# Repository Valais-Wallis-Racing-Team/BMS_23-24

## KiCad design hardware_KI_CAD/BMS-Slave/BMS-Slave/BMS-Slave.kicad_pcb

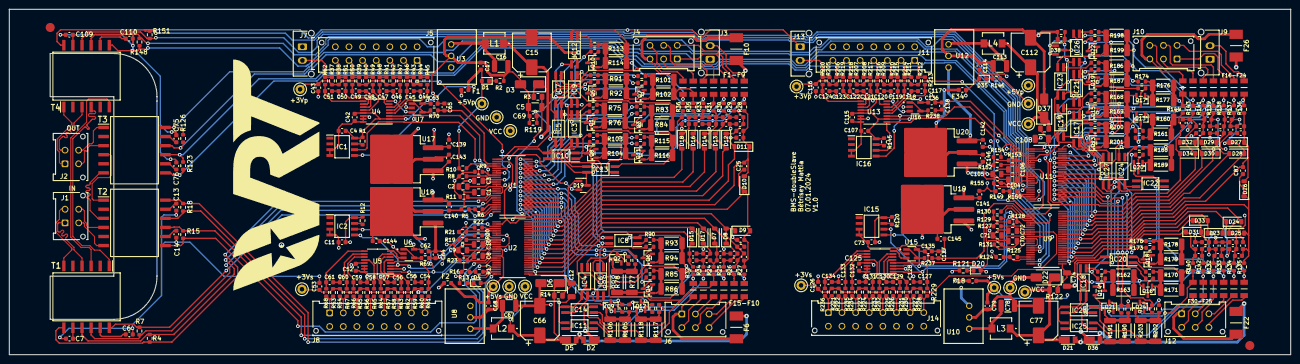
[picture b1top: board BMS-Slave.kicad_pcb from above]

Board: 4 copper layers, 282.0 x 76.0 mm, 568 parts (0 on the bottom side), 360 nets.

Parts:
C1, C2, C3, C8, C9, C10, C70, C71, C72, C104, C105, C106: 1uF/50V; C_0805_2012Metric
C4, C11, C17, C43, C53, C68, C73, C79, C107, C114, C116, C126, C139, C140, C141, C142: 100nF/50V; C_0603_1608Metric
C5, C12, C74, C108: 100nF/200V; C_1206_3216Metric
C6, C7, C13, C14, C75, C76, C109, C110: 100pF/50V; C_0603_1608Metric
C15, C66, C77, C112: 33uF/100V (8mm diameter); CP_Elec_8x10
C16, C67, C78, C113: 2.2uF/100V; C_1210_3225Metric
C18, C19, C20, C21, C22, C23, C24, C25, C26, C27, C28, C29, C30, C31, C32, C33, C34, C35, C36, C37, C38, C39, C40, C41, C44, C45, C46, C47, C48, C49, C50, C51, C54, C55, C56, C57, C58, C59, C60, C61, C64, C65, C80, C81, C82, C83, C84, C85, C86, C87, C88, C89, C90, C91, C92, C93, C94, C95, C96, C97, C98, C99, C100, C101, C102, C103, C117, C118, C119, C120, C121, C122, C123, C124, C127, C128, C129, C130, C131, C132, C133, C134, C137, C138: 10nF/100V; C_0603_1608Metric
C42, C52, C62, C63, C115, C125, C135, C136, C143, C144, C145, C146: 1uF/50V; C_0603_1608Metric
C69, C111: 10nF/50V; C_0603_1608Metric
D1, D4, D20, D35: LED Green TLMG1100-GS08; LED_0603_1608Metric
D2, D5, D21, D36: DFLS1100-7; POWERDI123_1
D3, D6, D22, D37: SMAJ54A-E3/61; D_SMA
D7, D8, D9, D10, D11, D12, D13, D14, D15, D16, D17, D18, D23, D24, D25, D26, D27, D28, D29, D30, D31, D32, D33, D34: SZMMSZ4692T1G; D_SOD-123
D19, D38: BAT54C,215; SOT-23
F1, F2, F18, F34: SF-0603SP063-2; Fuse_0603_1608Metric
F3, F4, F5, F7, F8, F9, F11, F12, F13, F14, F15, F16, F17, F19, F20, F21, F23, F24, F25, F27, F28, F29, F30, F31, F32, F33: 0466.250NR; FUSC3215X66N
F6, F10, F22, F26: 0448.500MR; FUSC6127X294N
FID1, FID2: Fiducial; fiducial 2mm with 3mm mask
IC1, IC2, IC15, IC16: M24M02-DWMN3TP_K; SOIC127P600X175-8N
IC3, IC4, IC5, IC6, IC7, IC8, IC9, IC10, IC11, IC12, IC13, IC14, IC17, IC18, IC19, IC20, IC21, IC22, IC23, IC24, IC25, IC26, IC27, IC28: ACPL-217-56BE; SOIC127P700X242-4N
J1, J2: 430450412; Molex_Micro-Fit_3.0_43045-0412_2x02_P3.00mm_Vertical
J3, J7, J9, J13: 43045-0212; Molex_Micro-Fit_3.0_43650-0215_1x02_P3.00mm_Vertical
J4, J6, J10, J12: Conn_01x06_Pin; Molex_Micro-Fit_3.0_43045-0612_2x03_P3.00mm_Vertical
J5, J11: Conn_01x14_Pin; Molex_Micro-Fit_3.0_43045-1412_2x07_P3.00mm_Vertical
J8, J14: Conn_01x16_Pin; Molex_Micro-Fit_3.0_43045-1612_2x08_P3.00mm_Vertical
L1, L2, L3, L4: 4.7uH; TCK176
Q1, Q2, Q3, Q4, Q5, Q6, Q7, Q8, Q9, Q10, Q11, Q12, Q13, Q14, Q15, Q16, Q17, Q18, Q19, Q20, Q21, Q22, Q23, Q24: NX2301P_215; SOT23_TO-236AB_NEX
R1, R10, R12, R21, R22, R37, R38, R39, R40, R41, R42, R43, R44, R53, R54, R55, R56, R57, R58, R59, R60, R119, R120, R129, R130, R145, R154, R204, R205, R206, R207, R208, R209, R210, R211, R212, R221, R222, R223, R224, R225, R226, R227, R228: 10k; R_0603_1608Metric
R2, R13, R121, R146: 270R; R_0603_1608Metric
R3, R14, R122, R147: 100R; R_0805_2012Metric
R4, R7, R15, R18, R123, R126, R148, R151: 120R; R_0603_1608Metric
R5, R8, R9, R16, R19, R20, R124, R127, R128, R149, R152, R153: 1k2; R_0603_1608Metric
R6, R17, R125, R150: 820R; R_0603_1608Metric
R11, R23, R131, R155: 1M; R_0603_1608Metric
R24, R25, R26, R27, R28, R29, R30, R31, R32, R33, R34, R35, R36, R45, R46, R47, R48, R49, R50, R51, R52, R61, R62, R63, R64, R65, R66, R67, R68, R69, R70, R132, R133, R134, R135, R136, R137, R138, R139, R140, R141, R142, R143, R144, R213, R214, R215, R216, R217, R218, R219, R220, R229, R230, R231, R232, R233, R234, R235, R236, R237, R238: 100R; R_0603_1608Metric
R71, R72, R79, R80, R87, R88, R95, R96, R97, R107, R108, R109, R156, R157, R164, R165, R172, R173, R180, R181, R182, R192, R193, R194: 3k3; R_0603_1608Metric
R73, R74, R81, R82, R89, R90, R98, R99, R100, R110, R111, R112, R158, R159, R166, R167, R174, R175, R183, R184, R185, R195, R196, R197: 150R; R_0603_1608Metric
R75, R76, R77, R78, R83, R84, R85, R86, R91, R92, R93, R94, R101, R102, R103, R104, R105, R106, R113, R114, R115, R116, R117, R118, R160, R161, R162, R163, R168, R169, R170, R171, R176, R177, R178, R179, R186, R187, R188, R189, R190, R191, R198, R199, R200, R201, R202, R203: 68R 1/3W; R_2010_5025Metric
T1, T2, T3, T4: HM2102NL; SOP200P1473X500-12N
TP1, TP2, TP3, TP4, TP5, TP6, TP7, TP8, TP9, TP10, TP11, TP12, TP13, TP14, TP15, TP16: TestPoint; TestPoint_Keystone_5000-5004_Miniature
U1, U2, U9, U11: LTC6811HG-1_PBF; SOP50P780X200-48N
U3, U8, U10, U12: TSR 0.6-4890WI; TSR 0.6-4850WI
U4, U5, U13, U14: ADG728BRUZ; TSSOP-16_4.4x5mm_P0.65mm
U6, U7, U15, U16: AD8628ARTZ-R2; SOT95P280X145-5N
U17, U18, U19, U20: LM1086ISX-5.0/NOPB; TO-263-3_TabPin2

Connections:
/slave1_of_2/EXT_DC_ISO_prim: C15.1, D2.1 (K), D3.1 (A1), L1.1, R3.1, TP4.1
/slave1_of_2/EXT_DC_ISO_sec: C66.1, D5.1 (K), D6.1 (A1), L2.1, R14.1, TP7.1
/slave1_of_2/GND: C1.2, C2.2, C3.2, C4.2, C5.2, C6.2, C7.2, C8.2, C9.2, C10.2, C11.2, C12.2, C13.2, C14.2, C15.2, C16.2, C17.1, C18.2, C20.2, C22.2, C24.2, C26.2, C28.2, C30.2, C32.2, C34.2, C36.2, C38.2, C40.2, C42.2, C43.2, C44.1, C45.1, C46.1, C47.1, C48.1, C49.1, C50.1, C51.1, C52.2, C53.2, C54.1, C55.1, C56.1, C57.1, C58.1, C59.1, C60.1, C61.1, C62.2, C63.2, C64.2, C65.2, C66.2, C67.2, C68.1, C69.2, C139.1, C140.1, C143.1, C144.1, D3.2 (A2), D6.2 (A2), F10.2, IC1.3 (E2), IC1.4 (VSS), IC2.3 (E2), IC2.4 (VSS), J5.8, J5.9, J5.10, J5.11, J5.12, J5.13, J5.14, J7.1, J8.9, J8.10, J8.11, J8.12, J8.13, J8.14, J8.15, J8.16, R2.2, R5.2, R13.2, R16.2, R119.2, TP5.1, TP8.1, U1.30 (V-), U1.31 (V-__1), U2.30 (V-), U2.31 (V-__1), U2.36 (DTEN), U3.2 (GND), U4.14 (GND), U4.15 (A1), U4.16 (A0), U5.14 (GND), U5.15 (A1), U5.16 (A0), U6.2, U7.2, U8.2 (GND), U17.1 (GND), U18.1 (GND)
/slave1_of_2/SCL1: IC1.6 (SCL), R8.2, U1.33 (GPIO5), U4.1 (SCL)
/slave1_of_2/SCL2: IC2.6 (SCL), R19.2, U2.33 (GPIO5), U5.1 (SCL)
/slave1_of_2/SDA1: IC1.5 (SDA), R9.2, U1.32 (GPIO4), U4.3 (SDA)
/slave1_of_2/SDA2: IC2.5 (SDA), R20.2, U2.32 (GPIO4), U5.3 (SDA)
/slave1_of_2/Temp_MUX_prim: C65.1, R70.2, U1.27 (GPIO1)
/slave1_of_2/Temp_MUX_sec: C64.1, R69.2, U2.27 (GPIO1)
/slave1_of_2/U_Analog_IN/OPA_TEMP_prim: U4.8 (D), U7.3
/slave1_of_2/U_Analog_IN/OPA_TEMP_sec: U5.8 (D), U6.3
/slave1_of_2/U_Analog_IN/T_sens0: J5.1, R44.2, R45.1
/slave1_of_2/U_Analog_IN/T_sens1: J5.2, R43.2, R46.1
/slave1_of_2/U_Analog_IN/T_sens2: J5.3, R42.2, R47.1
/slave1_of_2/U_Analog_IN/T_sens3: J5.4, R41.2, R48.1
/slave1_of_2/U_Analog_IN/T_sens4: J5.5, R40.2, R49.1
/slave1_of_2/U_Analog_IN/T_sens5: J5.6, R39.2, R50.1
/slave1_of_2/U_Analog_IN/T_sens6: J5.7, R38.2, R51.1
/slave1_of_2/U_Analog_IN/T_sens7: J7.2, R37.2, R52.1
/slave1_of_2/U_Analog_IN/T_sens8: J8.8, R60.2, R61.1
/slave1_of_2/U_Analog_IN/T_sens9: J8.7, R59.2, R62.1
/slave1_of_2/U_Analog_IN/T_sens10: J8.6, R58.2, R63.1
/slave1_of_2/U_Analog_IN/T_sens11: J8.5, R57.2, R64.1
/slave1_of_2/U_Analog_IN/T_sens12: J8.4, R56.2, R65.1
/slave1_of_2/U_Analog_IN/T_sens13: J8.3, R55.2, R66.1
/slave1_of_2/U_Analog_IN/T_sens14: J8.2, R54.2, R67.1
/slave1_of_2/U_Analog_IN/T_sens15: J8.1, R53.2, R68.1
/slave1_of_2/U_Connectors/Cell.0: F4.1, J4.6
/slave1_of_2/U_Connectors/Cell.1: F5.1, J4.2
/slave1_of_2/U_Connectors/Cell.2: F7.1, J4.5
/slave1_of_2/U_Connectors/Cell.3: F8.1, J4.1
/slave1_of_2/U_Connectors/Cell.4: F9.1, J4.4
/slave1_of_2/U_Connectors/Cell.5: F11.1, J3.2
/slave1_of_2/U_Connectors/Cell.6: F12.1, J6.6
/slave1_of_2/U_Connectors/Cell.7: F13.1, J6.3
/slave1_of_2/U_Connectors/Cell.8: F14.1, J6.5
/slave1_of_2/U_Connectors/Cell.9: F15.1, J6.2
/slave1_of_2/U_Connectors/Cell.10: F16.1, J6.4
/slave1_of_2/U_Connectors/Cell.11: F6.1, F17.1, J6.1
/slave1_of_2/U_Connectors/Cell.GND: F3.1, F10.1, J4.3
/slave1_of_2/U_Input_Fuses/Cell_Fused.0: F4.2, IC9.2 (K), Q10.2 (S), R35.1, R101.2, R102.2
/slave1_of_2/U_Input_Fuses/Cell_Fused.1: F5.2, IC7.2 (K), Q7.2 (S), R33.1, R91.2, R92.2
/slave1_of_2/U_Input_Fuses/Cell_Fused.2: F7.2, IC5.2 (K), Q5.2 (S), R31.1, R83.2, R84.2
/slave1_of_2/U_Input_Fuses/Cell_Fused.3: F8.2, IC3.2 (K), Q3.2 (S), R30.1, R75.2, R76.2
/slave1_of_2/U_Input_Fuses/Cell_Fused.4: F9.2, IC13.2 (K), Q1.2 (S), R29.1, R115.2, R116.2
/slave1_of_2/U_Input_Fuses/Cell_Fused.5: F11.2, IC10.2 (K), Q11.2 (S), R28.1, R103.2, R104.2
/slave1_of_2/U_Input_Fuses/Cell_Fused.6: F12.2, IC8.2 (K), Q8.2 (S), R27.1, R93.2, R94.2
/slave1_of_2/U_Input_Fuses/Cell_Fused.7: F13.2, IC6.2 (K), Q6.2 (S), R26.1, R85.2, R86.2
/slave1_of_2/U_Input_Fuses/Cell_Fused.8: F14.2, IC4.2 (K), Q4.2 (S), R25.1, R77.2, R78.2
/slave1_of_2/U_Input_Fuses/Cell_Fused.9: F15.2, IC14.2 (K), Q2.2 (S), R24.1, R117.2, R118.2
/slave1_of_2/U_Input_Fuses/Cell_Fused.10: F16.2, IC11.2 (K), Q12.2 (S), R34.1, R105.2, R106.2
/slave1_of_2/U_Input_Fuses/Cell_Fused.11: F17.2, Q9.2 (S), R32.1
/slave1_of_2/U_Input_Fuses/Cell_Fused.GND: F3.2, IC12.2 (K), R36.1, R113.2, R114.2
/slave1_of_2/U_Passive_Balancing/GLOBAL_BAL_FEEDBACK: C69.1, IC3.3 (E), IC4.3 (E), IC5.3 (E), IC6.3 (E), IC7.3 (E), IC8.3 (E), IC9.3 (E), IC10.3 (E), IC11.3 (E), IC12.3 (E), IC13.3 (E), IC14.3 (E), R119.1, U1.29 (GPIO3)
/slave1_of_2/U_Passive_Balancing/S1: R107.2, U1.25 (S1)
/slave1_of_2/U_Passive_Balancing/S2: R95.2, U1.23 (S2)
/slave1_of_2/U_Passive_Balancing/S3: R87.2, U1.21 (S3)
/slave1_of_2/U_Passive_Balancing/S4: R79.2, U1.19 (S4)
/slave1_of_2/U_Passive_Balancing/S5: R71.2, U1.17 (S5)
/slave1_of_2/U_Passive_Balancing/S6: R108.2, U1.15 (S6)
/slave1_of_2/U_Passive_Balancing/S7: R96.2, U1.13 (S7)
/slave1_of_2/U_Passive_Balancing/S8: R88.2, U1.11 (S8)
/slave1_of_2/U_Passive_Balancing/S9: R80.2, U1.9 (S9)
/slave1_of_2/U_Passive_Balancing/S10: R72.2, U1.7 (S10)
/slave1_of_2/U_Passive_Balancing/S11: R109.2, U1.5 (S11)
/slave1_of_2/U_Passive_Balancing/S12: R97.2, U1.3 (S12)
/slave1_of_2/U_Primary_ADBMS/C0: C41.2, D18.2 (A), R36.2, U1.26 (C0), U2.26 (C0)
/slave1_of_2/U_Primary_ADBMS/C1: C37.2, C40.1, C41.1, D16.2 (A), D18.1 (K), R35.2, U1.24 (C1), U2.24 (C1)
/slave1_of_2/U_Primary_ADBMS/C2: C33.2, C36.1, C37.1, D14.2 (A), D16.1 (K), R33.2, U1.22 (C2), U2.22 (C2)
/slave1_of_2/U_Primary_ADBMS/C3: C31.2, C32.1, C33.1, D13.2 (A), D14.1 (K), R31.2, U1.20 (C3), U2.20 (C3)
/slave1_of_2/U_Primary_ADBMS/C4: C29.2, C30.1, C31.1, D12.2 (A), D13.1 (K), R30.2, U1.18 (C4), U2.18 (C4)
/slave1_of_2/U_Primary_ADBMS/C5: C27.2, C28.1, C29.1, D11.2 (A), D12.1 (K), R29.2, U1.16 (C5), U2.16 (C5)
/slave1_of_2/U_Primary_ADBMS/C6: C25.2, C26.1, C27.1, D10.2 (A), D11.1 (K), R28.2, U1.14 (C6), U2.14 (C6)
/slave1_of_2/U_Primary_ADBMS/C7: C23.2, C24.1, C25.1, D9.2 (A), D10.1 (K), R27.2, U1.12 (C7), U2.12 (C7)
/slave1_of_2/U_Primary_ADBMS/C8: C21.2, C22.1, C23.1, D8.2 (A), D9.1 (K), R26.2, U1.10 (C8), U2.10 (C8)
/slave1_of_2/U_Primary_ADBMS/C9: C19.2, C20.1, C21.1, D7.2 (A), D8.1 (K), R25.2, U1.8 (C9), U2.8 (C9)
/slave1_of_2/U_Primary_ADBMS/C10: C18.1, C19.1, C39.2, D7.1 (K), D17.2 (A), R24.2, U1.6 (C10), U2.6 (C10)
/slave1_of_2/U_Primary_ADBMS/C11: C35.2, C38.1, C39.1, D15.2 (A), D17.1 (K), R34.2, U1.4 (C11), U2.4 (C11)
/slave1_of_2/U_Primary_ADBMS/C12: C34.1, C35.1, D15.1 (K), R32.2, U1.2 (C12), U2.2 (C12)
/slave1_of_2/U_Primary_ADBMS/IN_M1: R4.1, T1.7 (SEC_1), U1.41 (CSB/IMA)
/slave1_of_2/U_Primary_ADBMS/IN_P1: R4.2, T1.9 (SEC_3), U1.42 (SCK/IPA)
/slave1_of_2/U_Primary_ADBMS/OUT_M1: R7.1, T1.10 (SEC_4), U1.47 (IMB)
/slave1_of_2/U_Primary_ADBMS/OUT_P1: R7.2, T1.12 (SEC_6), U1.48 (IPB)
/slave1_of_2/U_Primary_ADBMS/isoSPI_IN+: J1.1, T1.4 (PRI_4)
/slave1_of_2/U_Primary_ADBMS/isoSPI_IN-: J1.2, T1.6 (PRI_6)
/slave1_of_2/U_Primary_ADBMS/isoSPI_OUT+: T1.1 (PRI_1), T4.4 (PRI_4)
/slave1_of_2/U_Primary_ADBMS/isoSPI_OUT-: T1.3 (PRI_3), T4.6 (PRI_6)
/slave1_of_2/U_Primary_ADBMS/prim3V3: C2.1, U1.35 (VREF1)
/slave1_of_2/U_Secondary_ADBMS/IN_M1: R15.1, T2.7 (SEC_1), U2.41 (CSB/IMA)
/slave1_of_2/U_Secondary_ADBMS/IN_P1: R15.2, T2.9 (SEC_3), U2.42 (SCK/IPA)
/slave1_of_2/U_Secondary_ADBMS/OUT_M1: R18.1, T2.10 (SEC_4), U2.47 (IMB)
/slave1_of_2/U_Secondary_ADBMS/OUT_P1: R18.2, T2.12 (SEC_6), U2.48 (IPB)
/slave1_of_2/U_Secondary_ADBMS/isoSPI_IN+: J1.4, T2.4 (PRI_4)
/slave1_of_2/U_Secondary_ADBMS/isoSPI_IN-: J1.3, T2.6 (PRI_6)
/slave1_of_2/U_Secondary_ADBMS/isoSPI_OUT+: T2.1 (PRI_1), T3.4 (PRI_4)
/slave1_of_2/U_Secondary_ADBMS/isoSPI_OUT-: T2.3 (PRI_3), T3.6 (PRI_6)
/slave1_of_2/U_Secondary_ADBMS/sec3v3: C9.1, U2.35 (VREF1)
/slave1_of_2/VBAT+: D2.2 (A), D5.2 (A), F6.2
/slave1_of_2/prim+3V: C3.1, C43.1, R37.1, R38.1, R39.1, R40.1, R41.1, R42.1, R43.1, R44.1, TP1.1, U1.34 (VREF2)
/slave1_of_2/prim+5V: C1.1, C4.1, C17.2, C42.1, C63.1, D1.2 (A), D19.2, F1.1, IC1.8 (VCC), R1.1, R8.1, R9.1, R10.1, R11.1, TP3.1, U1.36 (DTEN), U1.37 (VREG), U1.40 (ISOMD), U4.2 (~RESET), U4.13 (VDD), U7.5
/slave1_of_2/sec+3v: C10.1, C53.1, R53.1, R54.1, R55.1, R56.1, R57.1, R58.1, R59.1, R60.1, TP2.1, U2.34 (VREF2)
/slave1_of_2/sec+5v: C8.1, C11.1, C52.1, C62.1, C68.2, D4.2 (A), D19.1, F2.1, IC2.8 (VCC), R12.1, R19.1, R20.1, R21.1, R22.1, R23.1, TP6.1, U2.37 (VREG), U2.40 (ISOMD), U5.2 (~RESET), U5.13 (VDD), U6.5
/slave2_of_2/EXT_DC_ISO_prim: C112.1, D36.1 (K), D37.1 (A1), L4.1, R147.1, TP15.1
/slave2_of_2/EXT_DC_ISO_sec: C77.1, D21.1 (K), D22.1 (A1), L3.1, R122.1, TP11.1
/slave2_of_2/GND: C70.2, C71.2, C72.2, C73.2, C74.2, C75.2, C76.2, C77.2, C78.2, C79.1, C80.2, C82.2, C84.2, C86.2, C88.2, C90.2, C92.2, C94.2, C96.2, C98.2, C100.2, C102.2, C104.2, C105.2, C106.2, C107.2, C108.2, C109.2, C110.2, C111.2, C112.2, C113.2, C114.1, C115.2, C116.2, C117.1, C118.1, C119.1, C120.1, C121.1, C122.1, C123.1, C124.1, C125.2, C126.2, C127.1, C128.1, C129.1, C130.1, C131.1, C132.1, C133.1, C134.1, C135.2, C136.2, C137.2, C138.2, C141.1, C142.1, C145.1, C146.1, D22.2 (A2), D37.2 (A2), F26.2, IC15.3 (E2), IC15.4 (VSS), IC16.3 (E2), IC16.4 (VSS), J11.8, J11.9, J11.10, J11.11, J11.12, J11.13, J11.14, J13.1, J14.9, J14.10, J14.11, J14.12, J14.13, J14.14, J14.15, J14.16, R121.2, R124.2, R146.2, R149.2, R204.2, TP12.1, TP16.1, U9.30 (V-), U9.31 (V-__1), U9.36 (DTEN), U10.2 (GND), U11.30 (V-), U11.31 (V-__1), U12.2 (GND), U13.14 (GND), U13.15 (A1), U13.16 (A0), U14.14 (GND), U14.15 (A1), U14.16 (A0), U15.2, U16.2, U19.1 (GND), U20.1 (GND)
/slave2_of_2/SCL1: IC16.6 (SCL), R152.2, U11.33 (GPIO5), U13.1 (SCL)
/slave2_of_2/SCL2: IC15.6 (SCL), R127.2, U9.33 (GPIO5), U14.1 (SCL)
/slave2_of_2/SDA1: IC16.5 (SDA), R153.2, U11.32 (GPIO4), U13.3 (SDA)
/slave2_of_2/SDA2: IC15.5 (SDA), R128.2, U9.32 (GPIO4), U14.3 (SDA)
/slave2_of_2/Temp_MUX_prim: C138.1, R238.2, U11.27 (GPIO1)
/slave2_of_2/Temp_MUX_sec: C137.1, R237.2, U9.27 (GPIO1)
/slave2_of_2/U_Analog_IN/OPA_TEMP_prim: U13.8 (D), U16.3
/slave2_of_2/U_Analog_IN/OPA_TEMP_sec: U14.8 (D), U15.3
/slave2_of_2/U_Analog_IN/T_sens0: J11.1, R212.2, R213.1
/slave2_of_2/U_Analog_IN/T_sens1: J11.2, R211.2, R214.1
/slave2_of_2/U_Analog_IN/T_sens2: J11.3, R210.2, R215.1
/slave2_of_2/U_Analog_IN/T_sens3: J11.4, R209.2, R216.1
/slave2_of_2/U_Analog_IN/T_sens4: J11.5, R208.2, R217.1
/slave2_of_2/U_Analog_IN/T_sens5: J11.6, R207.2, R218.1
/slave2_of_2/U_Analog_IN/T_sens6: J11.7, R206.2, R219.1
/slave2_of_2/U_Analog_IN/T_sens7: J13.2, R205.2, R220.1
/slave2_of_2/U_Analog_IN/T_sens8: J14.8, R228.2, R229.1
/slave2_of_2/U_Analog_IN/T_sens9: J14.7, R227.2, R230.1
/slave2_of_2/U_Analog_IN/T_sens10: J14.6, R226.2, R231.1
/slave2_of_2/U_Analog_IN/T_sens11: J14.5, R225.2, R232.1
/slave2_of_2/U_Analog_IN/T_sens12: J14.4, R224.2, R233.1
/slave2_of_2/U_Analog_IN/T_sens13: J14.3, R223.2, R234.1
/slave2_of_2/U_Analog_IN/T_sens14: J14.2, R222.2, R235.1
/slave2_of_2/U_Analog_IN/T_sens15: J14.1, R221.2, R236.1
/slave2_of_2/U_Connectors/Cell.0: F20.1, J10.6
/slave2_of_2/U_Connectors/Cell.1: F21.1, J10.2
/slave2_of_2/U_Connectors/Cell.2: F23.1, J10.5
/slave2_of_2/U_Connectors/Cell.3: F24.1, J10.1
/slave2_of_2/U_Connectors/Cell.4: F25.1, J10.4
/slave2_of_2/U_Connectors/Cell.5: F27.1, J9.2
/slave2_of_2/U_Connectors/Cell.6: F28.1, J12.6
/slave2_of_2/U_Connectors/Cell.7: F29.1, J12.3
/slave2_of_2/U_Connectors/Cell.8: F30.1, J12.5
/slave2_of_2/U_Connectors/Cell.9: F31.1, J12.2
/slave2_of_2/U_Connectors/Cell.10: F32.1, J12.4
/slave2_of_2/U_Connectors/Cell.11: F22.1, F33.1, J12.1
/slave2_of_2/U_Connectors/Cell.GND: F19.1, F26.1, J10.3
/slave2_of_2/U_Input_Fuses/Cell_Fused.0: F20.2, IC23.2 (K), Q22.2 (S), R143.1, R186.2, R187.2
/slave2_of_2/U_Input_Fuses/Cell_Fused.1: F21.2, IC21.2 (K), Q19.2 (S), R141.1, R176.2, R177.2
/slave2_of_2/U_Input_Fuses/Cell_Fused.2: F23.2, IC19.2 (K), Q17.2 (S), R139.1, R168.2, R169.2
/slave2_of_2/U_Input_Fuses/Cell_Fused.3: F24.2, IC17.2 (K), Q15.2 (S), R138.1, R160.2, R161.2
/slave2_of_2/U_Input_Fuses/Cell_Fused.4: F25.2, IC27.2 (K), Q13.2 (S), R137.1, R200.2, R201.2
/slave2_of_2/U_Input_Fuses/Cell_Fused.5: F27.2, IC24.2 (K), Q23.2 (S), R136.1, R188.2, R189.2
/slave2_of_2/U_Input_Fuses/Cell_Fused.6: F28.2, IC22.2 (K), Q20.2 (S), R135.1, R178.2, R179.2
/slave2_of_2/U_Input_Fuses/Cell_Fused.7: F29.2, IC20.2 (K), Q18.2 (S), R134.1, R170.2, R171.2
/slave2_of_2/U_Input_Fuses/Cell_Fused.8: F30.2, IC18.2 (K), Q16.2 (S), R133.1, R162.2, R163.2
/slave2_of_2/U_Input_Fuses/Cell_Fused.9: F31.2, IC28.2 (K), Q14.2 (S), R132.1, R202.2, R203.2
/slave2_of_2/U_Input_Fuses/Cell_Fused.10: F32.2, IC25.2 (K), Q24.2 (S), R142.1, R190.2, R191.2
/slave2_of_2/U_Input_Fuses/Cell_Fused.11: F33.2, Q21.2 (S), R140.1
/slave2_of_2/U_Input_Fuses/Cell_Fused.GND: F19.2, IC26.2 (K), R144.1, R198.2, R199.2
/slave2_of_2/U_Passive_Balancing/GLOBAL_BAL_FEEDBACK: C111.1, IC17.3 (E), IC18.3 (E), IC19.3 (E), IC20.3 (E), IC21.3 (E), IC22.3 (E), IC23.3 (E), IC24.3 (E), IC25.3 (E), IC26.3 (E), IC27.3 (E), IC28.3 (E), R204.1, U11.29 (GPIO3)
/slave2_of_2/U_Passive_Balancing/S1: R192.2, U11.25 (S1)
/slave2_of_2/U_Passive_Balancing/S2: R180.2, U11.23 (S2)
/slave2_of_2/U_Passive_Balancing/S3: R172.2, U11.21 (S3)
/slave2_of_2/U_Passive_Balancing/S4: R164.2, U11.19 (S4)
/slave2_of_2/U_Passive_Balancing/S5: R156.2, U11.17 (S5)
/slave2_of_2/U_Passive_Balancing/S6: R193.2, U11.15 (S6)
/slave2_of_2/U_Passive_Balancing/S7: R181.2, U11.13 (S7)
/slave2_of_2/U_Passive_Balancing/S8: R173.2, U11.11 (S8)
/slave2_of_2/U_Passive_Balancing/S9: R165.2, U11.9 (S9)
/slave2_of_2/U_Passive_Balancing/S10: R157.2, U11.7 (S10)
/slave2_of_2/U_Passive_Balancing/S11: R194.2, U11.5 (S11)
/slave2_of_2/U_Passive_Balancing/S12: R182.2, U11.3 (S12)
/slave2_of_2/U_Primary_ADBMS/C0: C103.2, D34.2 (A), R144.2, U9.26 (C0), U11.26 (C0)
/slave2_of_2/U_Primary_ADBMS/C1: C99.2, C102.1, C103.1, D32.2 (A), D34.1 (K), R143.2, U9.24 (C1), U11.24 (C1)
/slave2_of_2/U_Primary_ADBMS/C2: C95.2, C98.1, C99.1, D30.2 (A), D32.1 (K), R141.2, U9.22 (C2), U11.22 (C2)
/slave2_of_2/U_Primary_ADBMS/C3: C93.2, C94.1, C95.1, D29.2 (A), D30.1 (K), R139.2, U9.20 (C3), U11.20 (C3)
/slave2_of_2/U_Primary_ADBMS/C4: C91.2, C92.1, C93.1, D28.2 (A), D29.1 (K), R138.2, U9.18 (C4), U11.18 (C4)
/slave2_of_2/U_Primary_ADBMS/C5: C89.2, C90.1, C91.1, D27.2 (A), D28.1 (K), R137.2, U9.16 (C5), U11.16 (C5)
/slave2_of_2/U_Primary_ADBMS/C6: C87.2, C88.1, C89.1, D26.2 (A), D27.1 (K), R136.2, U9.14 (C6), U11.14 (C6)
/slave2_of_2/U_Primary_ADBMS/C7: C85.2, C86.1, C87.1, D25.2 (A), D26.1 (K), R135.2, U9.12 (C7), U11.12 (C7)
/slave2_of_2/U_Primary_ADBMS/C8: C83.2, C84.1, C85.1, D24.2 (A), D25.1 (K), R134.2, U9.10 (C8), U11.10 (C8)
/slave2_of_2/U_Primary_ADBMS/C9: C81.2, C82.1, C83.1, D23.2 (A), D24.1 (K), R133.2, U9.8 (C9), U11.8 (C9)
/slave2_of_2/U_Primary_ADBMS/C10: C80.1, C81.1, C101.2, D23.1 (K), D33.2 (A), R132.2, U9.6 (C10), U11.6 (C10)
/slave2_of_2/U_Primary_ADBMS/C11: C97.2, C100.1, C101.1, D31.2 (A), D33.1 (K), R142.2, U9.4 (C11), U11.4 (C11)
/slave2_of_2/U_Primary_ADBMS/C12: C96.1, C97.1, D31.1 (K), R140.2, U9.2 (C12), U11.2 (C12)
/slave2_of_2/U_Primary_ADBMS/IN_M1: R148.1, T4.7 (SEC_1), U11.41 (CSB/IMA)
/slave2_of_2/U_Primary_ADBMS/IN_P1: R148.2, T4.9 (SEC_3), U11.42 (SCK/IPA)
/slave2_of_2/U_Primary_ADBMS/OUT_M1: R151.1, T4.10 (SEC_4), U11.47 (IMB)
/slave2_of_2/U_Primary_ADBMS/OUT_P1: R151.2, T4.12 (SEC_6), U11.48 (IPB)
/slave2_of_2/U_Primary_ADBMS/isoSPI_OUT+: J2.1, T4.1 (PRI_1)
/slave2_of_2/U_Primary_ADBMS/isoSPI_OUT-: J2.2, T4.3 (PRI_3)
/slave2_of_2/U_Primary_ADBMS/prim3V3: C105.1, U11.35 (VREF1)
/slave2_of_2/U_Secondary_ADBMS/IN_M1: R123.1, T3.7 (SEC_1), U9.41 (CSB/IMA)
/slave2_of_2/U_Secondary_ADBMS/IN_P1: R123.2, T3.9 (SEC_3), U9.42 (SCK/IPA)
/slave2_of_2/U_Secondary_ADBMS/OUT_M1: R126.1, T3.10 (SEC_4), U9.47 (IMB)
/slave2_of_2/U_Secondary_ADBMS/OUT_P1: R126.2, T3.12 (SEC_6), U9.48 (IPB)
/slave2_of_2/U_Secondary_ADBMS/isoSPI_OUT+: J2.4, T3.1 (PRI_1)
/slave2_of_2/U_Secondary_ADBMS/isoSPI_OUT-: J2.3, T3.3 (PRI_3)
/slave2_of_2/U_Secondary_ADBMS/sec3v3: C71.1, U9.35 (VREF1)
/slave2_of_2/VBAT+: D21.2 (A), D36.2 (A), F22.2
/slave2_of_2/prim+3V: C106.1, C116.1, R205.1, R206.1, R207.1, R208.1, R209.1, R210.1, R211.1, R212.1, TP13.1, U11.34 (VREF2)
/slave2_of_2/prim+5V: C104.1, C107.1, C114.2, C115.1, C136.1, D35.2 (A), D38.2, F34.1, IC16.8 (VCC), R145.1, R152.1, R153.1, R154.1, R155.1, TP14.1, U11.36 (DTEN), U11.37 (VREG), U11.40 (ISOMD), U13.2 (~RESET), U13.13 (VDD), U16.5
/slave2_of_2/sec+3v: C72.1, C126.1, R221.1, R222.1, R223.1, R224.1, R225.1, R226.1, R227.1, R228.1, TP9.1, U9.34 (VREF2)
/slave2_of_2/sec+5v: C70.1, C73.1, C79.2, C125.1, C135.1, D20.2 (A), D38.1, F18.1, IC15.8 (VCC), R120.1, R127.1, R128.1, R129.1, R130.1, R131.1, TP10.1, U9.37 (VREG), U9.40 (ISOMD), U14.2 (~RESET), U14.13 (VDD), U15.5
unnamed: D1.1 (K), R2.1
unnamed: D4.1 (K), R13.1
unnamed: D20.1 (K), R121.1
unnamed: D35.1 (K), R146.1
unnamed: IC1.7 (~WC), R1.2
unnamed: IC2.7 (~WC), R12.2
unnamed: IC3.1 (A), R73.2
unnamed: IC4.1 (A), R74.2
unnamed: IC5.1 (A), R81.2
unnamed: IC6.1 (A), R82.2
unnamed: IC7.1 (A), R89.2
unnamed: IC8.1 (A), R90.2
unnamed: IC9.1 (A), R98.2
unnamed: IC10.1 (A), R99.2
unnamed: D19.3, IC3.4 (C), IC4.4 (C), IC5.4 (C), IC6.4 (C), IC7.4 (C), IC8.4 (C), IC9.4 (C), IC10.4 (C), IC11.4 (C), IC12.4 (C), IC13.4 (C), IC14.4 (C)
unnamed: IC11.1 (A), R100.2
unnamed: IC12.1 (A), R110.2
unnamed: IC13.1 (A), R111.2
unnamed: IC14.1 (A), R112.2
unnamed: IC15.7 (~WC), R120.2
unnamed: IC16.7 (~WC), R145.2
unnamed: IC17.1 (A), R158.2
unnamed: D38.3, IC17.4 (C), IC18.4 (C), IC19.4 (C), IC20.4 (C), IC21.4 (C), IC22.4 (C), IC23.4 (C), IC24.4 (C), IC25.4 (C), IC26.4 (C), IC27.4 (C), IC28.4 (C)
unnamed: IC18.1 (A), R159.2
unnamed: IC19.1 (A), R166.2
unnamed: IC20.1 (A), R167.2
unnamed: IC21.1 (A), R174.2
unnamed: IC22.1 (A), R175.2
unnamed: IC23.1 (A), R183.2
unnamed: IC24.1 (A), R184.2
unnamed: IC25.1 (A), R185.2
unnamed: IC26.1 (A), R195.2
unnamed: IC27.1 (A), R196.2
unnamed: IC28.1 (A), R197.2
unnamed: Q1.1 (D), R73.1, R75.1, R76.1
unnamed: Q1.3 (G), R71.1
unnamed: Q2.1 (D), R74.1, R77.1, R78.1
unnamed: Q2.3 (G), R72.1
unnamed: Q3.1 (D), R81.1, R83.1, R84.1
unnamed: Q3.3 (G), R79.1
unnamed: Q4.1 (D), R82.1, R85.1, R86.1
unnamed: Q4.3 (G), R80.1
unnamed: Q5.1 (D), R89.1, R91.1, R92.1
unnamed: Q5.3 (G), R87.1
unnamed: Q6.1 (D), R90.1, R93.1, R94.1
unnamed: Q6.3 (G), R88.1
unnamed: Q7.1 (D), R98.1, R101.1, R102.1
unnamed: Q7.3 (G), R95.1
unnamed: Q8.1 (D), R99.1, R103.1, R104.1
unnamed: Q8.3 (G), R96.1
unnamed: Q9.1 (D), R100.1, R105.1, R106.1
unnamed: Q9.3 (G), R97.1
unnamed: Q10.1 (D), R110.1, R113.1, R114.1
unnamed: Q10.3 (G), R107.1
unnamed: Q11.1 (D), R111.1, R115.1, R116.1
unnamed: Q11.3 (G), R108.1
unnamed: Q12.1 (D), R112.1, R117.1, R118.1
unnamed: Q12.3 (G), R109.1
unnamed: Q13.1 (D), R158.1, R160.1, R161.1
unnamed: Q13.3 (G), R156.1
unnamed: Q14.1 (D), R159.1, R162.1, R163.1
unnamed: Q14.3 (G), R157.1
unnamed: Q15.1 (D), R166.1, R168.1, R169.1
unnamed: Q15.3 (G), R164.1
unnamed: Q16.1 (D), R167.1, R170.1, R171.1
unnamed: Q16.3 (G), R165.1
unnamed: Q17.1 (D), R174.1, R176.1, R177.1
unnamed: Q17.3 (G), R172.1
unnamed: Q18.1 (D), R175.1, R178.1, R179.1
unnamed: Q18.3 (G), R173.1
unnamed: Q19.1 (D), R183.1, R186.1, R187.1
unnamed: Q19.3 (G), R180.1
unnamed: Q20.1 (D), R184.1, R188.1, R189.1
unnamed: Q20.3 (G), R181.1
unnamed: Q21.1 (D), R185.1, R190.1, R191.1
unnamed: Q21.3 (G), R182.1
unnamed: Q22.1 (D), R195.1, R198.1, R199.1
unnamed: Q22.3 (G), R192.1
unnamed: Q23.1 (D), R196.1, R200.1, R201.1
unnamed: Q23.3 (G), R193.1
unnamed: Q24.1 (D), R197.1, R202.1, R203.1
unnamed: Q24.3 (G), R194.1
unnamed: R69.1, U6.1, U6.4
unnamed: R70.1, U7.1, U7.4
unnamed: R237.1, U15.1, U15.4
unnamed: R238.1, U16.1, U16.4
unnamed: C7.1, T1.8 (SEC_2)
unnamed: C6.1, T1.11 (SEC_5)
unnamed: C14.1, T2.8 (SEC_2)
unnamed: C13.1, T2.11 (SEC_5)
unnamed: C76.1, T3.8 (SEC_2)
unnamed: C75.1, T3.11 (SEC_5)
unnamed: C110.1, T4.8 (SEC_2)
unnamed: C109.1, T4.11 (SEC_5)
unnamed: R10.2, U1.28 (GPIO2)
unnamed: R6.2, U1.45 (IBIAS)
unnamed: R5.1, R6.1, U1.46 (ICMP)
unnamed: C5.1, R3.2, U1.1 (V+)
unnamed: R11.2, U1.39 (WDT)
unnamed: R22.2, U2.28 (GPIO2)
unnamed: R21.2, U2.29 (GPIO3)
unnamed: R17.2, U2.45 (IBIAS)
unnamed: R16.1, R17.1, U2.46 (ICMP)
unnamed: C12.1, R14.2, U2.1 (V+)
unnamed: R23.2, U2.39 (WDT)
unnamed: C16.1, L1.2, U3.1 (+VIN)
unnamed: C44.2, R45.2, U4.4 (S1)
unnamed: C45.2, R46.2, U4.5 (S2)
unnamed: C46.2, R47.2, U4.6 (S3)
unnamed: C47.2, R48.2, U4.7 (S4)
unnamed: C48.2, R49.2, U4.12 (S5)
unnamed: C49.2, R50.2, U4.11 (S6)
unnamed: C50.2, R51.2, U4.10 (S7)
unnamed: C51.2, R52.2, U4.9 (S8)
unnamed: C54.2, R61.2, U5.4 (S1)
unnamed: C55.2, R62.2, U5.5 (S2)
unnamed: C56.2, R63.2, U5.6 (S3)
unnamed: C57.2, R64.2, U5.7 (S4)
unnamed: C58.2, R65.2, U5.12 (S5)
unnamed: C59.2, R66.2, U5.11 (S6)
unnamed: C60.2, R67.2, U5.10 (S7)
unnamed: C61.2, R68.2, U5.9 (S8)
unnamed: C67.1, L2.2, U8.1 (+VIN)
unnamed: R130.2, U9.28 (GPIO2)
unnamed: R129.2, U9.29 (GPIO3)
unnamed: R125.2, U9.45 (IBIAS)
unnamed: R124.1, R125.1, U9.46 (ICMP)
unnamed: C74.1, R122.2, U9.1 (V+)
unnamed: R131.2, U9.39 (WDT)
unnamed: C78.1, L3.2, U10.1 (+VIN)
unnamed: C141.2, U10.3 (+VOUT), U19.3 (VI)
unnamed: R154.2, U11.28 (GPIO2)
unnamed: R150.2, U11.45 (IBIAS)
unnamed: R149.1, R150.1, U11.46 (ICMP)
unnamed: C108.1, R147.2, U11.1 (V+)
unnamed: R155.2, U11.39 (WDT)
unnamed: C113.1, L4.2, U12.1 (+VIN)
unnamed: C142.2, U12.3 (+VOUT), U20.3 (VI)
unnamed: C117.2, R213.2, U13.4 (S1)
unnamed: C118.2, R214.2, U13.5 (S2)
unnamed: C119.2, R215.2, U13.6 (S3)
unnamed: C120.2, R216.2, U13.7 (S4)
unnamed: C121.2, R217.2, U13.12 (S5)
unnamed: C122.2, R218.2, U13.11 (S6)
unnamed: C123.2, R219.2, U13.10 (S7)
unnamed: C124.2, R220.2, U13.9 (S8)
unnamed: C127.2, R229.2, U14.4 (S1)
unnamed: C128.2, R230.2, U14.5 (S2)
unnamed: C129.2, R231.2, U14.6 (S3)
unnamed: C130.2, R232.2, U14.7 (S4)
unnamed: C131.2, R233.2, U14.12 (S5)
unnamed: C132.2, R234.2, U14.11 (S6)
unnamed: C133.2, R235.2, U14.10 (S7)
unnamed: C134.2, R236.2, U14.9 (S8)
unnamed: C139.2, U3.3 (+VOUT), U17.3 (VI)
unnamed: C143.2, F1.2, U17.2 (VO)
unnamed: C140.2, U8.3 (+VOUT), U18.3 (VI)
unnamed: C144.2, F2.2, U18.2 (VO)
unnamed: C145.2, F18.2, U19.2 (VO)
unnamed: C146.2, F34.2, U20.2 (VO)

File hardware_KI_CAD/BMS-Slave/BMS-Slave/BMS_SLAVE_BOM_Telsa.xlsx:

Fournisseur | Nbr. | N° article | Référence | Valeur | Empreinte | Description | Fitted (X) | Generic (X) | Through-hole (X) | prix unitaire | prix total
BOM BMS-Slave |  |  |  |  |  |  |  |  |  | Liste actualisée le : 12.01.2024
Composants électriques et électroniques
 | 12 | generic | C1-C3, C8-C10, C70-C72, C104-C106 | 1uF/50V | Capacitor_SMD:C_0805_2012Metric | Capa 1uF/50V | X | X |  |  | 0
 | 16 | generic | C4, C11, C17, C43, C53, C68, C73, C79, C107, C114, C116, C126, C139-C142 | 100nF/50V | Capacitor_SMD:C_0603_1608Metric | Capa 100nF/50V | X | X |  |  | 0
 | 4 | generic | C5, C12, C74, C108 | 100nF/200V | Capacitor_SMD:C_1206_3216Metric | Capa 100nF/200V | X | X |  |  | 0
 | 8 | generic | C6, C7, C13, C14, C75, C76, C109, C110 | 100pF/50V | Capacitor_SMD:C_0603_1608Metric | Capa 100pF/50V | X | X |  |  | 0
Mouser | 4 | 80-EDH336M100A9MAA | C15, C66, C77, C112 | 33uF/100V | Capacitor_SMD:CP_Elec_8x10 | Capa électrolitique 33uF/100V | X |  |  | 0.61 | 2.44
 | 4 | generic | C16, C67, C78, C113 | 2.2uF/100V | Capacitor_SMD:C_1210_3225Metric | Capa 2.2uF/100V | X | X |  |  | 0
 | 84 | generic | C18-C41, C44-C51, C54-C61, C64, C65, C80-C103, C117-C124, C127-C134, C137, C138 | 10nF/100V | Capacitor_SMD:C_0603_1608Metric | Capa 10nF/100V | X | X |  |  | 0
 | 12 | generic | C42, C52, C62, C63, C115, C125, C135, C136, C143-C146 | 1uF/50V | Capacitor_SMD:C_0603_1608Metric | Capa 1uF/50V | X | X |  |  | 0
 | 2 | generic | C69, C111 | 10nF/50V | Capacitor_SMD:C_0603_1608Metric | Capa 10nF/50V | X | X |  |  | 0
Mouser | 4 | 78-TLMG1100 | D1, D4, D20, D35 | LED Green TLMG1100-GS08 | LED_0603_1608Metric | Standard LEDs - SMD Green Non-Diffused | X |  |  | 0.31 | 1.24
Mouser | 4 | 621-DFLS1100-7 | D2, D5, D21, D36 | DFLS1100-7 | PowerDI123 | Schottky Diodes & Rectifiers 1.0A 100V | X |  |  | 0.28999999999999998 | 1.1599999999999999
Mouser | 4 | 625-SMAJ54A-E3 | D3, D6, D22, D37 | SMAJ54A-E3/61 | SMA | ESD Suppressors / TVS Diodes 400W 54V | X |  |  | 0.37 | 1.48
Mouser | 24 | 863-SZMMSZ4692T1G | D7-D18, D23-D34 | SZMMSZ4692T1G | SOD-123 | Zener Diodes ZEN REG 0.5W 6.8V | X |  |  | 0.35 | 8.3999999999999986
Mouser | 2 | 771-BAT54C-T/R | D19, D38 | BAT54C,215 | SOT-23 | Schottky Diodes & Rectifiers BAT54C/SOT23/TO-236AB | X |  |  | 0.15 | 0.3
Mouser | 4 | 652-SF-0603SP063-2 | F1, F2, F18, F34 | SF-0603SP063-2 | Fuse_0603_1608Metric | Surface Mount Fuses .63A 32V TIME DELAY | X |  |  | 0.39 | 1.56
Mouser | 26 | 576-0466.250NR | F3-F5, F7-F9, F11-F17, F19-F21, F23-F25, F27-F33 | 0466.250NR | 0466.250NR:FUSC3215X66N | Surface Mount Fuses .25A 125V VERY FAST ACTING | X |  |  | 0.62 | 16.12
Mouser | 4 | 576-0448.500MR | F6, F10, F22, F26 | 0448.500MR | 0448_500MR:FUSC6127X294N | Surface Mount Fuses 125VAC 0.5A .38ohms 448 NANO2 | X |  |  | 1.1599999999999999 | 4.6399999999999997
Mouser | 4 | 511-M24M02-DWMN3TP/K | IC1, IC2, IC15, IC16 | M24M02-DWMN3TP_K | SO-8 | EEPROM Automotive 2-Mbit serial I2C bus EEPROM 1 MHz clock | X |  |  | 3.89 | 15.56
Mouser | 24 | 630-ACPL-217-56BE | IC3-IC14, IC17-IC28 | ACPL-217-56BE | SO-4 | Transistor Output Optocouplers 3000Vrms 50% CTR | X |  |  | 0.59 | 15.56
Mouser | 2 | 538-43045-0412 | J1, J2 | 430450412 | Molex_Micro-Fit_3.0_43045-0412_2x02_P3.00mm_Vertical | Molex micro-fit 3.0 4position 2 rows vertical | X |  | X | 0.94 | 14.16
Mouser | 4 | 538-430-45-0212 | J3, J7, J9, J13 | 43045-0212 | Molex_Micro-Fit_3.0_43650-0215_1x02_P3.00mm_Vertical | Molex micro-fit 3.0 2position 1row vertical | X |  | X | 0.75 | 1.88
Mouser | 4 | 538-43045-0612 | J4, J6, J10, J12 | 43045-0612 | Molex_Micro-Fit_3.0_43045-0612_2x03_P3.00mm_Vertical | Molex micro-fit 3.0 6position 2 rows vertical | X |  | X | 1.19 | 3
Mouser | 2 | 538-43045-1412 | J5, J11 | 43045-1412 | Molex_Micro-Fit_3.0_43045-1412_2x07_P3.00mm_Vertical | Molex micro-fit 3.0 14position 2 rows vertical | X |  | X | 2.59 | 4.76
Mouser | 2 | 538-43045-1612 | J8, J14 | 43045-1612 | Molex_Micro-Fit_3.0_43045-1612_2x08_P3.00mm_Vertical | Molex micro-fit 3.0 16position 2 rows vertical | X |  | X | 2.98 | 5.18
Mouser | 4 | 495-TCK-176 | L1-L4 | 4.7uH | TCK176 | Power Inductors - SMD 4.7uH 52mOhm 4.5A Inductor | X |  |  | 3.49 | 5.96
Mouser | 24 | 771-NX2301P215 | Q1-Q24 | NX2301P_215 (P-chanel MOSFET) | SOT23 | MOSFET NX2301P/SOT23 | X |  |  | 0.28000000000000003 | 13.96
 | 44 | generic | R1, R10, R12, R21, R22, R37-R44, R53-R60, R119, R120, R129, R130, R145, R154, R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 | 10k | Resistor_SMD:R_0603_1608Metric | Resistor SMD 10k 0603 | X | X |  |  | 6.7200000000000006
 | 4 | generic | R2, R13, R121, R146 | 270R | Resistor_SMD:R_0603_1608Metric | Resistor SMD 270R 0603 | X | X |  |  | 0
 | 4 | generic | R3, R14, R122, R147 | 100R | Resistor_SMD:R_0805_2012Metric | Resistor SMD 100R 0803 | X | X |  |  | 0
 | 8 | generic | R4, R7, R15, R18, R123, R126, R148, R151 | 120R | Resistor_SMD:R_0603_1608Metric | Resistor SMD 120R 0603 | X | X |  |  | 0
 | 12 | generic | R5, R8, R9, R16, R19, R20, R124, R127, R128, R149, R152, R153 | 1k2 | Resistor_SMD:R_0603_1608Metric | Resistor SMD 1k2 0603 | X | X |  |  | 0
 | 4 | generic | R6, R17, R125, R150 | 820R | Resistor_SMD:R_0603_1608Metric | Resistor SMD 820R 0603 | X | X |  |  | 0
 | 4 | generic | R11, R23, R131, R155 | 1M | Resistor_SMD:R_0603_1608Metric | Resistor SMD 1M 0603 | X | X |  |  | 0
 | 62 | generic | R24-R36, R45-R52, R61-R70, R132-R144, R213-R220, R229-R238 | 100R | Resistor_SMD:R_0603_1608Metric | Resistor SMD 100R 0603 | X | X |  |  | 0
 | 24 | generic | R71, R72, R79, R80, R87, R88, R95-R97, R107-R109, R156, R157, R164, R165, R172,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 | 3k3 | Resistor_SMD:R_0603_1608Metric | Resistor SMD 3k3 0603 | X | X |  |  | 0
 | 24 | generic | R73, R74, R81, R82, R89, R90, R98-R100, R110-R112, R158, R159, R166, R167, R174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 | 150R | Resistor_SMD:R_0603_1608Metric | Resistor SMD 150R 0603 | X | X |  |  | 0
 | 48 | generic | R75-R78, R83-R86, R91-R94, R101-R106, R113-R118, R160-R163, R168-R171, R176-R17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 | 68R 1/3W | Resistor_SMD:R_2010_5025Metric | Resistor SMD 68R 2010 1/3W | X | X |  |  | 0
Farnell | 4 | 3861166 | T1-T4 | HM2102NL | SOP200P1473X500-12N | Common Mode Chokes / Filters MDL DUAL XFMR-CMC AEC-Q200 | X |  |  | 5.97 | 0
 | 16 |  | TP1-TP16 | TestPoint | TestPoint:TestPoint_Keystone_5000-5004_Miniature | test points |  |  | X |  | 23.88
Mouser | 4 | 584-LTC6811HG-1#PBF | U1, U2, U9, U11 | LTC6811HG-1_PBF | SOP50P780X200-48N | Battery Management 12 Channel Multicell Battery Monitor with Daisy Chain Interf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 | X |  |  | 18.68 | 0
DigiKex | 4 | 1951-TSR0.6-4890WI-ND | U3, U8, U10, U12 | TSR 0.6-4890WI | TSR 0.6-4850WI | DC/DC converter 14V to 72V in 9V out | X |  | X | 9.34 | 74.72
Mouser | 4 | 584-ADG728BRUZ | U4, U5, U13, U14 | ADG728BRUZ | TSSOP-16_4.4x5mm_P0.65mm | Multiplexer Switch ICs SERIAL I2C, 8-ch MUX | X |  |  | 5.63 | 37.36
Mouser | 4 | 584-AD8628ARTZ-R2 | U6, U7, U15, U16 | AD8628ARTZ-R2 | SOT-23-5 | SP Amp Chopper Stabilization Single R-R I/O Â±2.5V/5V 5-Pin SOT-23 T/R | X |  |  | 4.01 | 22.52
Mouser | 4 | 926-LM1086ISX50NOPB | U17-U20 | LM1086ISX-5.0/NOPB | TO-263-3 | LDO Voltage Regulators 5V 1.5A LDO Positve Reg | X |  |  | 1.89
 |  |  |  |  |  | Prix total final : |  |  |  |  | 282.55999999999995
